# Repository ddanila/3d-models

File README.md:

# 3D models

Canonical CAD sources for printable parts and visual reconstructions, primarily authored in
[OpenSCAD](https://openscad.org/).

Each model lives in its own directory under `models/`. A model directory has
a canonical `model.scad` entry point; generated STL and preview files live next
to it:

```text
models/
  model-name/
    model.scad
    model-name.stl
    part-lid.scad   # optional additional printable part
    model-name-lid.stl
    assembly.scad   # optional assembled preview scene
    preview.png
    preview-lid.png
    preview-assembly.png
    README.md       # optional model-specific notes
```

Shared OpenSCAD modules can live under `lib/`. Keep them outside `models/` so
the batch scripts do not treat them as standalone models.

Related models can share a group directory, such as `models/pk8010-korvet/`.
Each model inside the group keeps its own directory, source, STL, and preview.

## Requirements

- `openscad-nightly` or `openscad`
- ImageMagick (`magick`) or macOS `sips` for downscaling preview renders

## Commands

```bash
# Open one model interactively, by directory name or path.
./scripts/open.sh model-name
./scripts/open.sh models/model-name/model.scad
./scripts/open.sh pk8010-korvet/pk8010-korvet-side-lid

# Validate every model without changing committed artifacts.
./scripts/check-render.sh

# Regenerate each model's binary STL.
./scripts/export-stls.sh

# Regenerate each model's preview image.
./scripts/render-previews.sh
```

The batch commands recursively discover `model.scad` and optional
`part-*.scad` printable parts under `models/`, including group directories.
An `assembly.scad` scene
is rendered to `preview-assembly.png` when present, and printable parts receive
their own `preview-<part>.png` image.

## Physical verification

The primary distinction is **printed and verified** versus **not physically
verified**. See the [model/part status catalogue](MODEL-STATUS.md) and its
machine-readable [evidence registry](model-status.json). Visual acceptance and
successful exports do not establish physical fit. No part is promoted without
recorded print/fit evidence for its exact files.

This repository is the source of truth. DAC consumes versioned meshes, dimensions,
materials and verification metadata from here; geometry corrections belong here.

## Models

- [Juku](models/juku/) — printed and verified keycap; top/bottom cases,
  split bottom panels and legs
- [USB serial-adapter case](models/usb-serial-adapter-case/) — open-top case
  for the DIYMORE FT232BM/BL USB to RS232/UART TTL/RS485 adapter
- [DIP-28 chip tray](models/dip28-chip-tray/) — stackable four-chip tray for
  DIP-28 EEPROM and EPROM packages
- [РГ1Н loopback-connector case](models/rg1n-loopback-case/) — compact two-piece case
  for a wired 12-contact РГ1Н-1-4 loopback connector
- [ПК8010 Корвет](models/pk8010-korvet/) — right-side button, lid, and prototype ↑/8 and SHIFT keycaps
- [Oral-B five-brush stand](models/oral-b-five-brush-stand/) — flat shelf
  mounting base with five original-shaped supports and two screw holes
- [Robotron 1715M](models/robotron-1715m/) — museum reconstruction and its
  [display base ring](models/robotron-1715m/display-base-ring/), a protective
  insert with Ø174 mm outside, 3.5 mm radial wall and 5 mm height

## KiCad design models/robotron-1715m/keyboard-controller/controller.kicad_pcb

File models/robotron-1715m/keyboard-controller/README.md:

# Keyboard controller reconstruction

The root KiCad files describe the reference circuit and partial historical PCB.
`reference/` contains a separate proposed implementation of the same netlist.
Its geometry is not specimen evidence; dimensions, package adapters, device dynamics
and specimen timing remain unqualified. Neither variant is fabrication-ready.

## Review

Open `assembly-review.scad` for the detailed museum controller. Press F5 and Home;
set `side="bottom"` for its underside. `show_mounts` and `show_shield` restore the
surrounding hardware. `review.scad` shows the native electrical geometry separately.
Cyan artwork is unassigned and makes no connectivity claim.

Open `controller.kicad_pro` in KiCad 10 to edit the electrical reconstruction.
Unplaced components are parked outside the outline. Board dimensions remain
estimates, not specimen measurements. Exports use millimetres
and a common top-view frame; transforms and conventions are in `generated/layout.json`.

Open [the connection-review sheet](review/connection-review.html) for annotated
serial-output and X1 evidence, reference endpoints and distinguishing observations.
X1 serves the key matrix and LEDs; XT1 is the host cable. Edit the review questions
in `connection-review.json`, then run `python3 tools/connection_review.py`.
The generator reads canonical route/pin evidence and does not modify the PCB.
Projected search circles include held-out registration checks; they locate
occlusions and do not establish joints, layer transitions or connectivity.
`clock-continuation.json` records the resistor-bank fit, exposed top spans and
outer underside lane used by the clock connection review. Hidden spans remain
open joins; these observations do not assign a clock net or filter winding.
`output-assembly.json` records the primary filter envelope, visible joint rows and
raised wire arcs. Its generated visual assembly has no electrical pin assignments;
XT1's inherited native coordinates remain reference placeholders.
`cable-copper.json` records an anonymous underside graph; the generated report
retains connected groups, winding-pairing alternatives and registration checks.
Its board projection is illustrative and must not become numbered pads or native
electrical routes while registration and terminal identities remain unresolved.
`supply-review.json` selects canonical supply observations and held-out resistor
checks for that report. Filter predictions are outside the fits’ anchor hulls;
local fit agreement does not identify a winding or connect the shield to ground.
`filter-registration.json` matches the primary filter joint rows using held-out
inner joints. The generated local fit is bounded by the outer joints; projected
underside spans are not top copper or native electrical routes.

## Proposed reference PCB

Open `reference/controller.kicad_pcb` for the proposed layout and
`reference/review.scad` for its electrical geometry. Orange copper is proposed;
blue geometry retains an exact match to a historical source item. The historical
board and its evidence ledger remain separate. Reference completion does not
reduce unresolved historical joins.

Edit `reference/implementation.json` for proposed placements and routing constraints.
Use `tools/reference_board.py --prepare /tmp/robotron-reference/controller.kicad_pcb`
with KiCad Python to generate a starting board and DSN from the retained historical
input snapshot. The routing boundary is
inset to respect native edge clearance; disable the router's automatic neckdown.
The retained `reference/routing-receipt.json` identifies the router and inputs,
including the historical-board snapshot used for routing. Later historical
evidence updates do not rewrite that input or reroute the reference board.
Import a session with `--import-session FILE --input-board FILE --output-board FILE`;
this rejects changes to terminal identities or placements beyond interchange
precision, then applies the explicit mechanical drill changes in
`reference/package-adjustments.json`. Those changes preserve pad copper and routing
and still require native DRC. Then run `tools/reference_board.py` to export and check the committed
reference board, or `--check` for standard-Python freshness validation.

The reference filter assembly uses a proposed shared core with explicit winding
paths. Core dimensions and turns are mechanical design assumptions; they do not
set measured inductance, coupling or installed winding identity.

The proposed discrete and filter footprints are electrical adapters. Their semantic
pin order is explicit; they do not establish original hole entries, installed
orientation, winding identity or mechanical fit. The existing HDL comparisons
apply to the shared schematic connectivity, not the proposed copper's parasitics.

## Authorities

| Information | Editable source / generated review |
| --- | --- |
| Components, numbered pins and nets | `controller.kicad_sch`, local `kbd.kicad_sym`; `generated/connectivity.json` |
| Outline, footprints, holes and copper | `controller.kicad_pcb`; `generated/layout.json` and `generated/controller.scad` |
| Source provenance, variants and unresolved interpretations | `evidence.json`, `component-evidence.json` |
| Photo observations and registration | `photo-landmarks.json`, `bottom-landmarks.json`; generated registration JSON/SVG |
| Route provenance tied to native geometry | `route-evidence.json` |
| Assembly and mechanical estimates | `../specimen-details.scad` |
| Current ERC/DRC findings and export hashes | `generated/qualification.json`, `generated/manifest.json` |

Keep derived inventories in these artifacts. Git history records implementation
changes; this guide records the workflow and interpretation limits.

## Evidence boundaries

The primary museum board and comparison photographs are distinct specimens.
`evidence.json` pins their sources, markings and hashes. Comparison photographs
can clarify construction but require independent registration and an explicit
routing comparison before transferring geometry. The museum ROM was replaced;
its contents remain unread. A comparison ROM label does not identify either dump.

The Zander circuit is the digital reference. Published WR/RD and oscillator
variants remain separate in `referenceVariants`; do not combine them to fit the
emulator. Factory placement drawings establish reference identities where visible.
The matrix and lamps beyond X1 are external to the controller reconstruction.

Top-photo fits and bounded local underside fits support placement review. Global
underside registration remains unqualified. `top-copper-landmarks.json` and
`generated/top-registration.json` bound top copper independently of raised lead
observations; failed extrapolation checks remain visible. Raised leads and sockets can hide hole
centres; a successful local fit cannot establish copper attachment or board scale.
The [distributed registration review](reference/package-reviews/distributed-registration/assessment.json)
records the remaining transverse-scale ambiguity. Use the
[measurement targets](reference/package-reviews/registration-measurements/assessment.json)
to obtain independent constraints before refitting and applying the existing gate.
Package and perspective alternatives remain in `reference/package-reviews/`.
The [EFS standard](reference/efs-form-constraints.json) supplies a shared hole
pattern, but the [chamber review](reference/package-reviews/efs-chambers/assessment.json)
does not identify the primary specimen's installed form. Neither a nominal package
fit nor comparison-specimen dimensions authorize historical pad moves.
The eye-based fit holds out independent solder eyes and composes with qualified
underside placement only inside the intersection of their domains. Eye matches
do not establish net identity; nearby lanes must still be traced independently.
Superseded CPU clock and BR2 interpretations remain in `evidence.json:routeReviews`.
No withdrawn CLK assignment is restored merely because nearby traces align.

Body-only photo observations and package dimensions are recorded in
`component-evidence.json`, with device drawing sources in `packageReferences`.
They support visual estimates without assigning electrical pads.
`generated/layout.json:visualNetworks` and `visualAxials` export unplaced bodies
and raised lead observations separately. Their leads stop above the board without
invented holes, solder joints or terminal numbering. Raised lead ends
do not establish hidden holes, and drawing-view pin order does not establish
installed orientation. Preserve component asset credits during migration.

BR1 separates oscillator and CPU clock; BR2 separates reset source and CPU reset.
Their terminal numbers are reconstruction identifiers. Observed bridge geometry
can be represented as unassigned artwork before source/CPU terminal order is
resolved; do not attach guessed pads or nets to make it look complete. Generated
`layout.json:visualBridges` preserves these wire observations independently of
native footprints; review views show them in cyan. Virtual bridge isolation
is tested digitally, but the reviewed sources do not prescribe physical bridge
opening. Closed-link continuity alone cannot establish source-side terminal order.

Every historical native copper UUID requires an observed, inferred or unresolved review,
source hashes, a locator and `geometrySha256`. Geometry or net changes invalidate
the review. Observed tracks require their side's photo; observed vias require both
sides. This enforces provenance completeness, not the truth of an interpretation.
Unassigned photo artwork is not electrical copper.

`bus-review.json` retains partial bus paths with unresolved cross-side joins.
Its reference nets and terminal pairs are review targets, not assigned copper
or complete connections. `generated/bus-review.json` adds a local cross-side
search overlay for ROM-side eyes beneath the installed CPU body. Latch reviews
retain separate candidate eyes and covered exits. Neither identifies a via
or establishes continuity. Assigned cross-side joints carry separate top and
bottom registration checks; solder-obscured attachments and unmeasured via
dimensions remain inferred.
Before promotion, verify the photographed centreline,
pad positions and local registration independently; a model short alone does
not identify which of those is wrong.

`generated/connector-review.json` checks X1's native reference pads against
locally registered underside joints. `generated/connector-terminals.json` retains
row-order alternatives constrained by resistor and COL11 attachments; the two
row directions are tested independently. Assembly leads consume native positions
for mapped contacts. Owner inspection identifies A8 as present, soldered and
unrouted; its isolated native pad has no net and remains absent from the reference
schematic. Raised top-side bends are not hole centres; housing
dimensions, lead heights and hole diameters remain estimates.

## Native routing audit

`generated/routing-audit.json` reports same-net copper islands, their terminals,
route evidence groups and KiCad unconnected items. It includes off-board
placeholder pads. Use remaining pad-group links and fully connected multi-pin
nets to track native routing separately from photo reconstruction and simulation;
floating track fragments do not count as connected pads.

## Regenerate and check

From this directory, use Python with KiCad's `pcbnew` module for native export
and integration tests. Set `KICAD_CLI` if necessary. On macOS:

```sh
/Applications/KiCad/KiCad.app/Contents/Frameworks/Python.framework/Versions/3.9/bin/python3 tools/export.py
/Applications/KiCad/KiCad.app/Contents/Frameworks/Python.framework/Versions/3.9/bin/python3 tools/test_kicad.py
python3 tools/export.py --check
python3 tools/test_export.py
python3 tools/photo_registration.py
```

`photo_registration.py --apply --refs A1 ...` applies explicitly selected fits
only after independent landmarks pass. Regenerate exports after applying fits.
CI runs standard-Python freshness checks and a separate native
job using the [KiCad 10 stable Ubuntu packages](https://www.kicad.org/download/ubuntu/).
The native job records tool versions and regenerates only temporary copies; it
does not replace the committed exports. Unsupported zones, blind vias, internal
tracks and invalid outlines fail explicitly. ERC's RD_N and SHIELD exceptions
are recorded individually; outstanding DRC findings remain failures.

After geometry changes, use `../tools/export.py --parts` with the affected part
names, refresh all controller mesh receipts when shared SCAD inputs change, then
run `../tools/test_controller_mesh_contract.py`, `../tools/export-downloads.py`
and `../tools/check-metadata.py`. Review both sides before accepting new baselines.
Commit CAD before running the museum sync scripts; they reject dirty or stale
sources. Compatible revisions belong in the museum source manifests.

Digital comparisons and specimen evidence collection are documented in the
museum's [status guide](https://github.com/ddanila/dac/blob/main/docs/robotron/keyboard-controller-progress.md)
and [verification guide](https://github.com/ddanila/dac/blob/main/docs/robotron/keyboard-controller-verification.md). Logical reference agreement does not
qualify analog behavior, exact CPU cycle timing or specimen firmware.

### Populated reference assembly

Capacitor package hypotheses live in `reference/capacitor-package-*.json`. Run
`tools/capacitor_package_review.py --candidate <file> --out <directory>`
(from this directory) to check board and enclosure fit without adopting them.
`--pitch-offset` samples the published pitch tolerance; `--check` verifies retained
source freshness. Receipts in `reference/package-reviews/` own results and scope.
Package fit does not settle capacitor polarity or electrical substitution.

Open `reference/review.scad` with `show_components=true`. `reference/assembly.json`
defines proposed package choices; `tools/reference_assembly.py` derives numbered
lead paths and body poses from the routed pads, reusing the pinned DIP bodies and
manufacturer package dimensions. `reference/capacitor-polarity.json` binds proposed
can polarity to reference nets and pinned reset diagnostics; it does not assign
installed polarity. Regenerate with that tool; use `--check` to reject
stale exports. `reference/signal-paths.json` supplies netlist-checked walkthroughs
for the museum.

The generated review checks body envelopes, leads against foreign body envelopes, board
overhang, nominal drill allowance and 3D lead-to-lead surface clearance.
Intentional bridge/same-net contacts are separate from unintended contacts.
`tools/reference_enclosure.py` renders the PCB substrate and populated assembly
against the modeled case, supports, mounts and matrix board. Raised-component and
misaligned-mounting controls must collide. It retains source-bound results in `reference/enclosure-review.json`;
`--check` verifies freshness without rerendering. These nominal checks do not
qualify manufacturing tolerances or measured enclosure fit. Circular lead bends
use the explicit reference-design radius and chord-error budget in `reference/assembly.json`.
Lead clearance checks conservatively include that approximation error.
`assemblyAllowances` declares independent proposed body, core, lead and hole
budgets. Expanded-envelope results are separate from nominal results, including
enclosure checks with a deliberately colliding control; these are design assumptions,
not measured process tolerances.
R2 remains a package surrogate; shared-core magnetic coupling is unmeasured. These reference adapters do not establish historical
footprints or fabrication readiness.

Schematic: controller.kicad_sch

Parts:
A1: 7406; DIP-14_W7.62mm
A2.1, A2.2, A2.3: DL003; DIP-14_W7.62mm
A4: I8282; DIP-20_W7.62mm
A5: U880; DIP-40_W15.24mm
A6: DL074; DIP-14_W7.62mm
A7: DL000; DIP-14_W7.62mm
A8: U556_2716; DIP-24_W15.24mm
BR1, BR2: BRIDGE
C1: 220p
C2, C4: 10u
C3.1, C3.2: 47u
C5.1, C5.2, C5.3, C5.4, C5.5: 47n
C6: 470p
L1.1, L1.2, L1.3, L1.4: CHOKE
R1: 8x910
R2: 8x4k7
R3: 22k; R_Axial_DIN0207_L6.3mm_D2.5mm_P10.16mm_Horizontal
R4.1, R4.2, R4.3: 220; R_Axial_DIN0207_L6.3mm_D2.5mm_P10.16mm_Horizontal
R5: 10k; R_Axial_DIN0207_L6.3mm_D2.5mm_P10.16mm_Horizontal
R6.1, R6.3, R6.4, R6.5, R6.6: 1k; R_Axial_DIN0207_L6.3mm_D2.5mm_P10.16mm_Horizontal
R7: 3k3; R_Axial_DIN0207_L6.3mm_D2.5mm_P10.16mm_Horizontal
R8: 47k; R_Axial_DIN0207_L6.3mm_D2.5mm_P10.16mm_Horizontal
R9.1, R9.2, R9.3, R9.4, R9.5, R9.6, R9.7, R9.8, R9.9: 3k9; R_Axial_DIN0207_L6.3mm_D2.5mm_P10.16mm_Horizontal
R10.1, R10.2, R10.3: 560; R_Axial_DIN0207_L6.3mm_D2.5mm_P10.16mm_Horizontal
R11.1, R11.2: 130; R_Axial_DIN0207_L6.3mm_D2.5mm_P10.16mm_Horizontal
V1.1, V1.2, V2: DIODE
V3.1, V3.2: SC236D
V4.1, V4.2, V4.3, V4.4, V4.5, V4.6, V4.7, V4.8, V4.9: SC308C
X1: MATRIX_CONNECTOR
XT1: KEYBOARD_CABLE

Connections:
/+5V: A1.14 (+5V), A2.1.14 (+5V), A2.2.14 (+5V), A2.3.14 (+5V), A4.20 (+5V), A5.11 (+5V), A6.14 (+5V), A7.14 (+5V), A8.21 (+5V), A8.24 (+5V), C3.1.1 (+5V), C3.2.1 (+5V), C5.1.1 (+5V), C5.2.1 (+5V), C5.3.1 (+5V), C5.4.1 (+5V), C5.5.1 (+5V), L1.3.1 (+5V), R2.1 (+5V), R3.1 (+5V), R4.1.1 (+5V), R5.1 (+5V), R6.1.1 (+5V), R6.3.1 (+5V), R6.4.1 (+5V), R6.5.1 (+5V), R6.6.1 (+5V), R9.9.1 (+5V), R10.1.1 (+5V), R10.2.1 (+5V), R10.3.1 (+5V), V2.A (+5V), V3.1.C (+5V), V4.1.E (+5V), V4.2.E (+5V), V4.3.E (+5V), V4.4.E (+5V), V4.5.E (+5V), V4.6.E (+5V), V4.7.E (+5V), V4.8.E (+5V), V4.9.E (+5V), X1.A7 (+5V)
/A0: A2.3.9 (A0), A2.3.10 (A0), A5.30 (A0), A8.8 (A0)
/A1: A1.9 (A1), A5.31 (A1), A8.7 (A1)
/A2: A2.1.9 (A2), A2.1.10 (A2), A5.32 (A2), A8.6 (A2)
/A3: A2.1.1 (A3), A2.1.2 (A3), A5.33 (A3), A8.5 (A3)
/A4: A1.13 (A4), A5.34 (A4), A8.4 (A4)
/A5: A2.1.12 (A5), A2.1.13 (A5), A5.35 (A5), A8.3 (A5)
/A6: A1.11 (A6), A5.36 (A6), A8.2 (A6)
/A7: A2.2.1 (A7), A2.2.2 (A7), A5.37 (A7), A8.1 (A7)
/A8: A2.3.12 (A8), A2.3.13 (A8), A5.38 (A8), A8.23 (A8)
/A9: A2.3.4 (A9), A2.3.5 (A9), A5.39 (A9), A8.22 (A9)
/A10: A2.3.1 (A10), A2.3.2 (A10), A5.40 (A10), A8.19 (A10)
/A11: A2.1.4 (A11), A2.1.5 (A11), A5.1 (A11)
/A12: A2.2.12 (A12), A2.2.13 (A12), A5.2 (A12)
/A13: A5.3 (A13), A6.12 (A13)
/A14: A5.4 (A14), A6.2 (A14)
/A15: A2.2.9 (A15), A2.2.10 (A15), A5.5 (A15)
/BASE0: R2.3 (BASE0), R9.3.2 (BASE0), V4.3.B (BASE0)
/BASE1: R2.4 (BASE1), R9.5.2 (BASE1), V4.4.B (BASE1)
/BASE2: R2.8 (BASE2), R9.6.2 (BASE2), V4.8.B (BASE2)
/BASE3: R2.9 (BASE3), R9.7.2 (BASE3), V4.7.B (BASE3)
/BASE4: R2.5 (BASE4), R9.8.2 (BASE4), V4.1.B (BASE4)
/BASE5: R2.7 (BASE5), R9.4.2 (BASE5), V4.6.B (BASE5)
/BASE6: R2.2 (BASE6), R9.2.2 (BASE6), V4.2.B (BASE6)
/BASE7: R2.6 (BASE7), R9.1.2 (BASE7), V4.5.B (BASE7)
/BUSRQ_N: A5.25 (BUSRQ_N), R6.5.2 (BUSRQ_N), X1.A9 (BUSRQ_N)
/CABLE_5V: L1.3.2 (CABLE_5V), XT1.B4 (CABLE_5V)
/CABLE_DATEN: L1.4.2 (CABLE_DATEN), XT1.A1 (CABLE_DATEN)
/CABLE_GND: L1.2.2 (CABLE_GND), XT1.A3 (CABLE_GND)
/CABLE_TAKT: L1.1.2 (CABLE_TAKT), XT1.B2 (CABLE_TAKT)
/CLK: A5.6 (CLK), BR1.2 (CLK), R10.3.2 (CLK)
/COL0: A2.3.8 (COL0), X1.A11 (COL0)
/COL1: A1.8 (COL1), X1.A13 (COL1)
/COL2: A2.1.8 (COL2), X1.B10 (COL2)
/COL3: A2.1.3 (COL3), X1.B9 (COL3)
/COL4: A1.12 (COL4), X1.B1 (COL4)
/COL5: A2.1.11 (COL5), X1.A2 (COL5)
/COL6: A1.10 (COL6), X1.B3 (COL6)
/COL7: A2.2.3 (COL7), X1.B12 (COL7)
/COL8: A2.3.11 (COL8), X1.A3 (COL8)
/COL9: A2.3.6 (COL9), X1.A10 (COL9)
/COL10: A2.3.3 (COL10), X1.A12 (COL10)
/COL11: A2.1.6 (COL11), X1.B8 (COL11)
/COL12: A2.2.11 (COL12), X1.B4 (COL12)
/CPU_PULLUP: A5.16 (CPU_PULLUP), A5.17 (CPU_PULLUP), A5.24 (CPU_PULLUP), R6.4.2 (CPU_PULLUP)
/D0: A1.3 (D0), A4.19 (D0), A5.14 (D0), A8.9 (D0)
/D1: A4.18 (D1), A5.15 (D1), A8.10 (D1)
/D2: A4.17 (D2), A5.12 (D2), A8.11 (D2)
/D3: A4.16 (D3), A5.8 (D3), A8.13 (D3)
/D4: A4.15 (D4), A5.7 (D4), A8.14 (D4)
/D5: A4.14 (D5), A5.9 (D5), A8.15 (D5)
/D6: A4.13 (D6), A5.10 (D6), A8.16 (D6)
/D7: A4.12 (D7), A5.13 (D7), A8.17 (D7)
/FF_PULLUP: A6.1 (FF_PULLUP), A6.4 (FF_PULLUP), A6.10 (FF_PULLUP), A6.13 (FF_PULLUP), R6.6.2 (FF_PULLUP)
/GND: A1.7 (GND), A2.1.7 (GND), A2.2.7 (GND), A2.3.7 (GND), A4.10 (GND), A5.29 (GND), A6.7 (GND), A7.7 (GND), A8.12 (GND), A8.18 (GND), C3.1.2 (GND), C3.2.2 (GND), C4.2 (GND), C5.1.2 (GND), C5.2.2 (GND), C5.3.2 (GND), C5.4.2 (GND), C5.5.2 (GND), L1.2.1 (GND), R1.1 (GND), R4.2.2 (GND), R7.2 (GND), R8.2 (GND)
/IORQ_N: A2.2.4 (IORQ_N), A2.2.5 (IORQ_N), A5.20 (IORQ_N)
/IO_ACTIVE: A2.2.6 (IO_ACTIVE), A4.11 (IO_ACTIVE), A6.3 (IO_ACTIVE), A6.11 (IO_ACTIVE), R9.9.2 (IO_ACTIVE)
/LATCH_OE_N: A2.2.8 (LATCH_OE_N), A4.9 (LATCH_OE_N), R6.3.2 (LATCH_OE_N)
/LED_CAPS: R11.2.2 (LED_CAPS), X1.A6 (LED_CAPS)
/LED_CAPS_N: A6.6 (LED_CAPS_N), R11.2.1 (LED_CAPS_N)
/LED_SISO: R11.1.2 (LED_SISO), X1.A5 (LED_SISO)
/LED_SISO_N: A6.8 (LED_SISO_N), R11.1.1 (LED_SISO_N)
/MREQ_N: A5.19 (MREQ_N), A8.20 (MREQ_N)
/OSC1: A7.4 (OSC1), A7.5 (OSC1), A7.11 (OSC1), R4.3.1 (OSC1)
/OSC2: A7.6 (OSC2), A7.9 (OSC2), A7.10 (OSC2), C6.2 (OSC2)
/OSC_OUT: A7.8 (OSC_OUT), BR1.1 (OSC_OUT)
/OSC_RC: A7.12 (OSC_RC), A7.13 (OSC_RC), C6.1 (OSC_RC), R4.3.2 (OSC_RC)
/RD_N: A5.21 (RD_N)
/RESET_BASE: C1.1 (RESET_BASE), R6.1.2 (RESET_BASE), V3.2.C (RESET_BASE), V4.9.B (RESET_BASE)
/RESET_BIAS: R5.2 (RESET_BIAS), V1.1.A (RESET_BIAS), V3.2.B (RESET_BIAS)
/RESET_BIAS_LOW: C2.1 (RESET_BIAS_LOW), R3.2 (RESET_BIAS_LOW), V1.1.K (RESET_BIAS_LOW), V1.2.A (RESET_BIAS_LOW)
/RESET_DIODE_TOP: R4.1.2 (RESET_DIODE_TOP), V1.2.K (RESET_DIODE_TOP)
/RESET_EMITTERS: R7.1 (RESET_EMITTERS), V3.1.E (RESET_EMITTERS), V3.2.E (RESET_EMITTERS)
/RESET_N: A5.26 (RESET_N), BR2.2 (RESET_N)
/RESET_OUT: BR2.1 (RESET_OUT), C1.2 (RESET_OUT), C2.2 (RESET_OUT), R4.2.1 (RESET_OUT), V4.9.C (RESET_OUT)
/RESET_RC: C4.1 (RESET_RC), R8.1 (RESET_RC), V2.K (RESET_RC), V3.1.B (RESET_RC)
/ROW0: R9.3.1 (ROW0), X1.B6 (ROW0)
/ROW1: R9.5.1 (ROW1), X1.B2 (ROW1)
/ROW2: R9.6.1 (ROW2), X1.B7 (ROW2)
/ROW3: R9.7.1 (ROW3), X1.A1 (ROW3)
/ROW4: R9.8.1 (ROW4), X1.A4 (ROW4)
/ROW5: R9.4.1 (ROW5), X1.B5 (ROW5)
/ROW6: R9.2.1 (ROW6), X1.B11 (ROW6)
/ROW7: R9.1.1 (ROW7), X1.B13 (ROW7)
/SENSE0: A4.1 (SENSE0), R1.9 (SENSE0), V4.3.C (SENSE0)
/SENSE1: A4.2 (SENSE1), R1.8 (SENSE1), V4.4.C (SENSE1)
/SENSE2: A4.3 (SENSE2), R1.7 (SENSE2), V4.8.C (SENSE2)
/SENSE3: A4.4 (SENSE3), R1.6 (SENSE3), V4.7.C (SENSE3)
/SENSE4: A4.5 (SENSE4), R1.5 (SENSE4), V4.1.C (SENSE4)
/SENSE5: A4.6 (SENSE5), R1.4 (SENSE5), V4.6.C (SENSE5)
/SENSE6: A4.7 (SENSE6), R1.3 (SENSE6), V4.2.C (SENSE6)
/SENSE7: A4.8 (SENSE7), R1.2 (SENSE7), V4.5.C (SENSE7)
/SHIELD: XT1.A5 (SHIELD)
/TA_DATEN: A1.4 (TA_DATEN), L1.4.1 (TA_DATEN), R10.2.2 (TA_DATEN)
/TA_TAKT: A1.2 (TA_TAKT), L1.1.1 (TA_TAKT), R10.1.2 (TA_TAKT)
/WR_N: A1.1 (WR_N), A5.22 (WR_N)

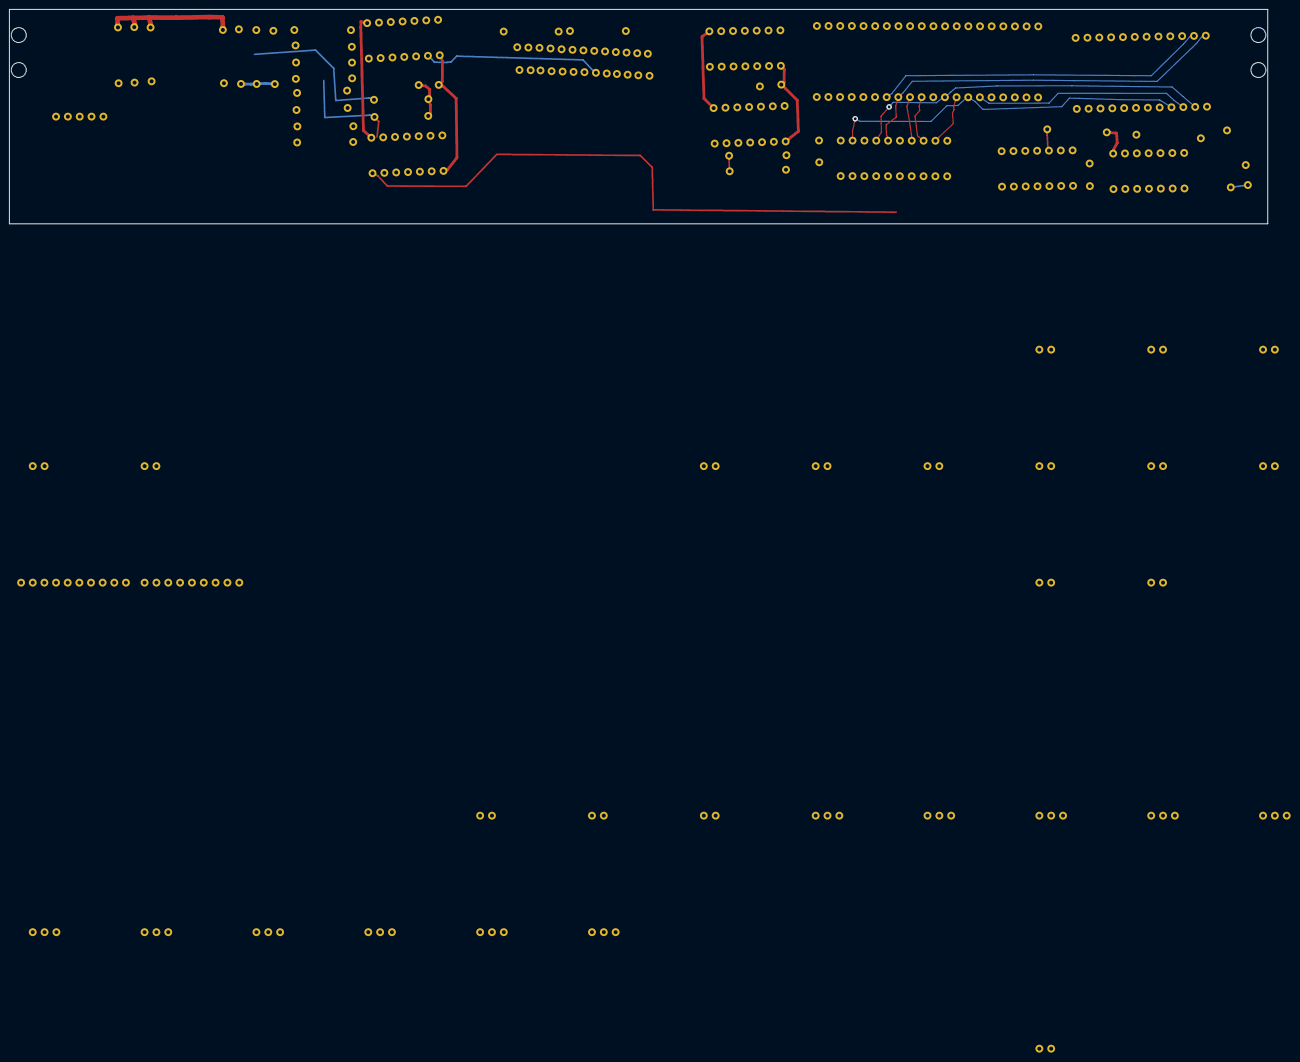
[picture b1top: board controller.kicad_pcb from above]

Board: 2 copper layers, 270.0 x 46.0 mm, 74 parts (0 on the bottom side), 94 nets.

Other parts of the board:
H1, H2, H3, H4: Photo estimated mounting hole
